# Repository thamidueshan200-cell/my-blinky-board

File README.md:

# my-blinky-board
This is a simple 555-timer based LED blinker PCB designed using KiCad. It is my first hardware project, and I have completed the DRC checks and generated the manufacturing files.

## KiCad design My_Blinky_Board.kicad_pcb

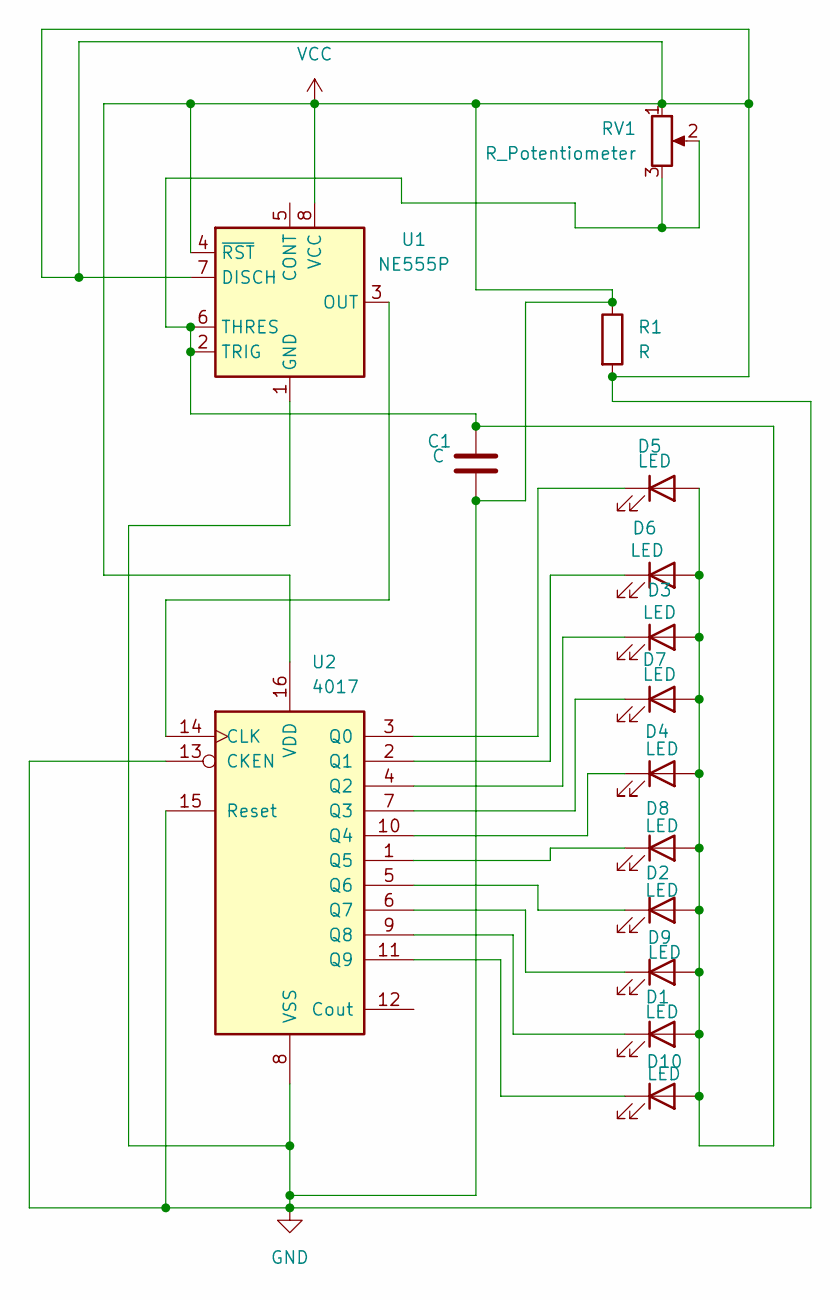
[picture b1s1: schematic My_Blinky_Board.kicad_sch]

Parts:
C1: C
D1, D2, D3, D4, D5, D6, D7, D8, D9, D10: LED
R1: R
RV1: R_Potentiometer
U1: NE555P; DIP-8_W7.62mm
U2: 4017

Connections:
GND: C1.2, R1.1, R1.2, RV1.1, U1.1 (GND), U1.4 (~RST), U1.7 (DISCH), U1.8 (VCC), U2.8 (VSS), U2.13 (CKEN), U2.15 (Reset), U2.16 (VDD)
unnamed: C1.1, D1.2 (A), D2.2 (A), D3.2 (A), D4.2 (A), D5.2 (A), D6.2 (A), D7.2 (A), D8.2 (A), D9.2 (A), D10.2 (A), RV1.2, RV1.3, U1.2 (TRIG), U1.6 (THRES)
unnamed: D1.1 (K), U2.9 (Q8)
unnamed: D2.1 (K), U2.5 (Q6)
unnamed: D3.1 (K), U2.4 (Q2)
unnamed: D4.1 (K), U2.10 (Q4)
unnamed: D5.1 (K), U2.3 (Q0)
unnamed: D6.1 (K), U2.2 (Q1)
unnamed: D7.1 (K), U2.7 (Q3)
unnamed: D8.1 (K), U2.1 (Q5)
unnamed: D9.1 (K), U2.6 (Q7)
unnamed: D10.1 (K), U2.11 (Q9)
unnamed: U1.3 (OUT), U2.14 (CLK)

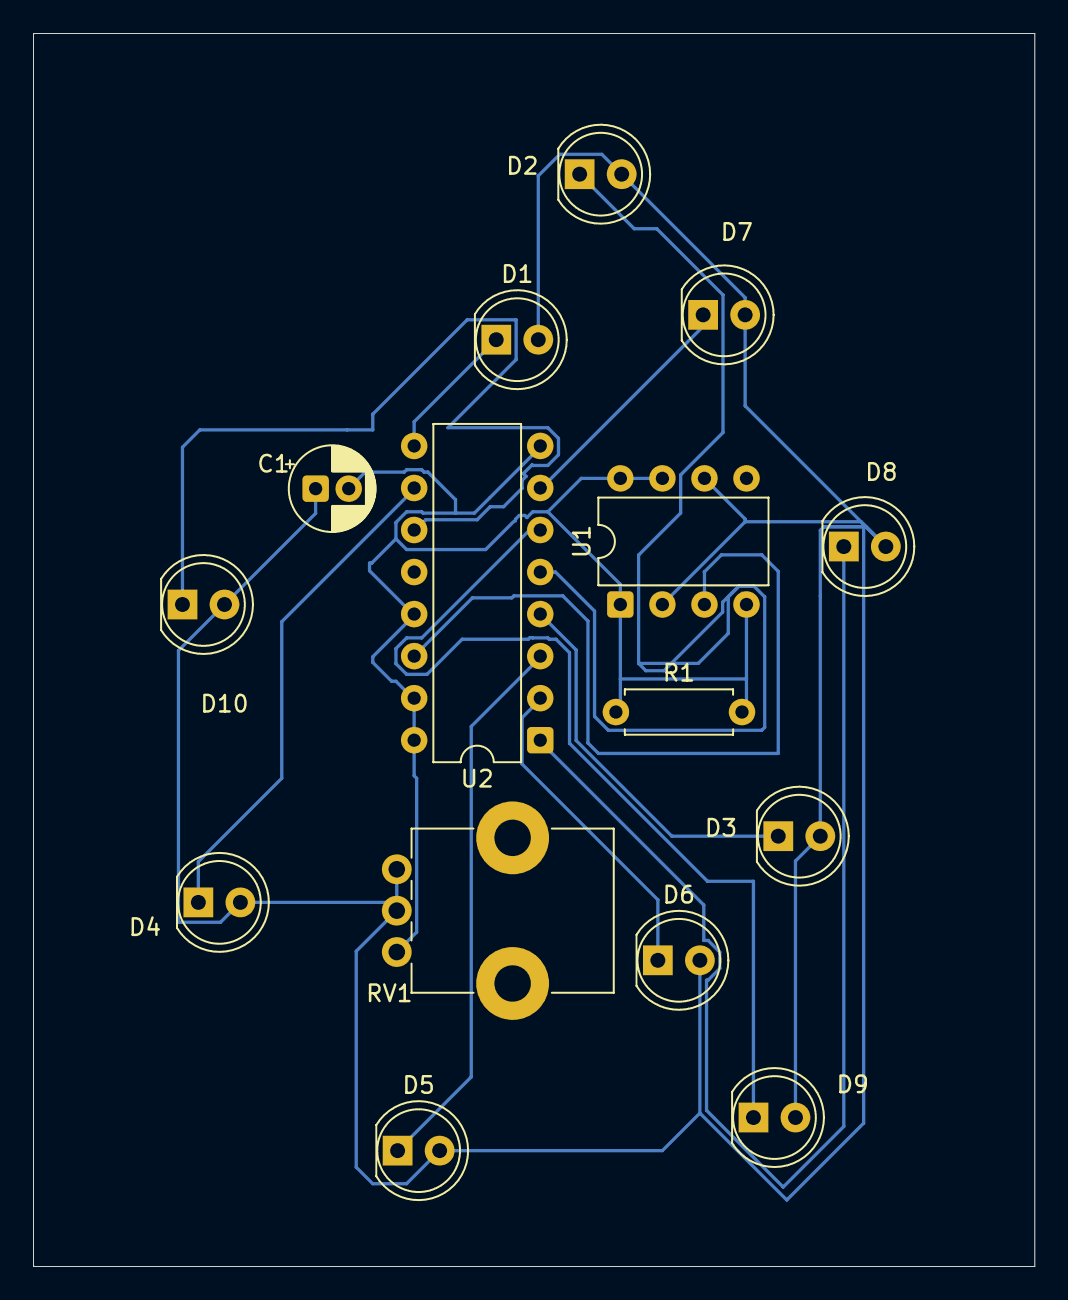
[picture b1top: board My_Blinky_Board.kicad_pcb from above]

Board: 2 copper layers, 60.5 x 74.5 mm, 15 parts (0 on the bottom side), 13 nets.
